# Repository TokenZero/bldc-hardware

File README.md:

VESC – Open Source ESC
=============

Custom board-mount version of the VESC 4.12

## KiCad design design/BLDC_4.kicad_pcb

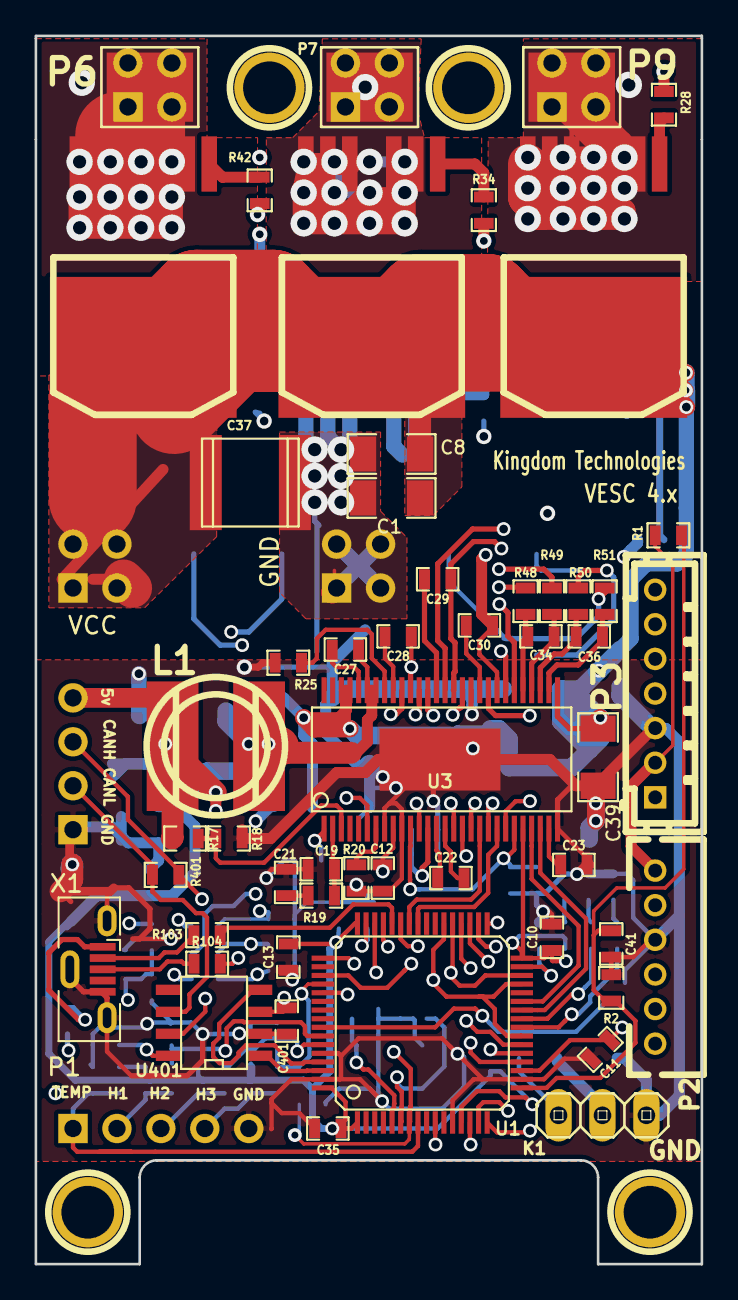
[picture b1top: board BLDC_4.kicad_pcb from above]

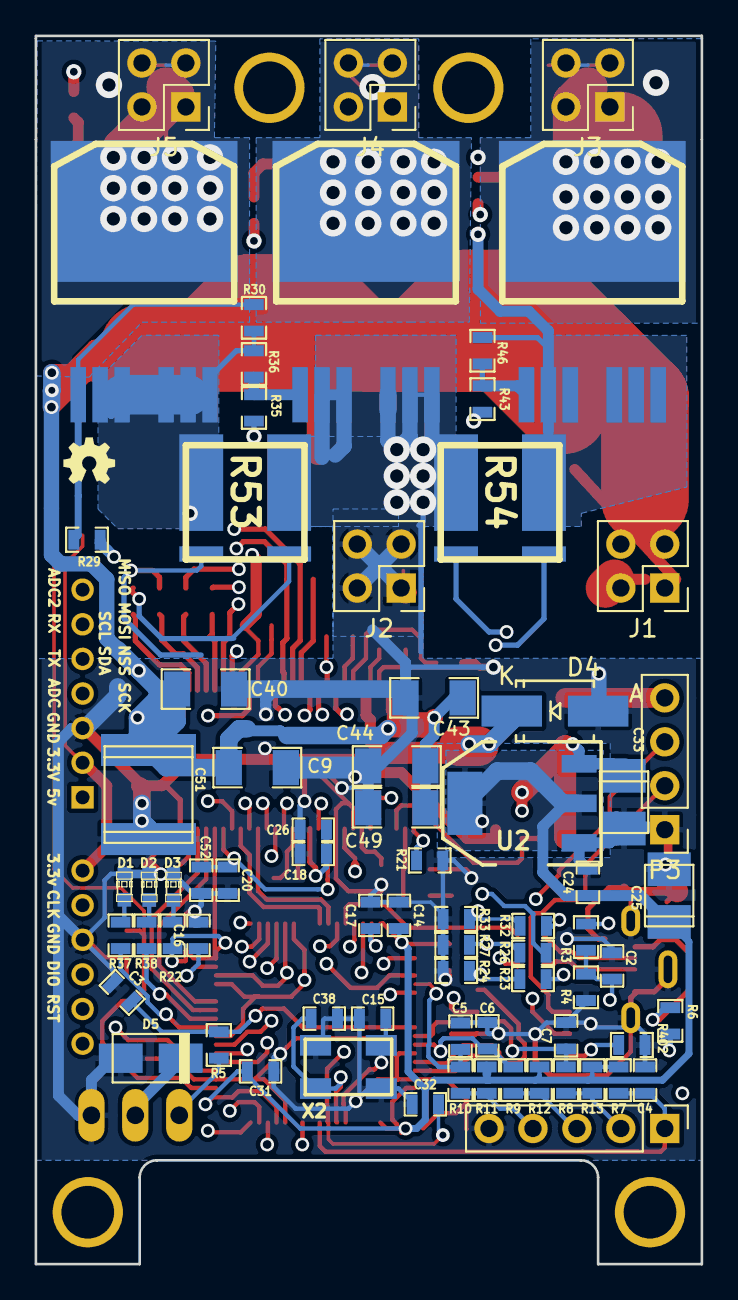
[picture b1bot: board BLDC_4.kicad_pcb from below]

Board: 4 copper layers, 38.5 x 71.0 mm, 129 parts (73 on the bottom side), 96 nets.

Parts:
1PIN, 1PIN#2, 1PIN#3, 1PIN#4: P***; 1pin
C1, C8, C9, C39, C40, C43, C44, C49: 10u,50V; SMD-1206
C2, C3, C27, C32: 100n; SMD-0603_c
C4, C5, C6, C7: 4n7; SMD-0603_c
C10, C11, C12, C13, C14, C16, C17, C18, C20, C23, C24, C26, C31, C35, C41, C52, C401: 2.2u; SMD-0603_c
C15, C38: 15p; SMD-0603_c
C19: 120p; SMD-0603_c
C21: 6.8n; SMD-0603_c
C22: 22n; SMD-0603_c
C25, C33: 100u; c_tant_B
C28, C29, C30: 220n; SMD-0603_c
C34, C36: 2.2n; SMD-0603_c
C37: 15u,100V; c_2220
C51: 15u, 100v; c_2220
D1: GREEN; LED-0603
D2: RED; LED-0603
D3: LED; LED-0603
D4: DIODESCH; SMA_Handsoldering
D5: TVS 5V; do214ac
J1: VCC_IN; PinHeader_2x02_P2.54mm_Vertical
J2: GND_IN; PinHeader_2x02_P2.54mm_Vertical
J3, J4, J5: PinHeader_2x02_P2.54mm_Vertical
K1: SERVO; pinhead-1X03
L1: 22u; inductor_smd_8x5mm
P1: PinHeader_1x05_P2.54mm_Vertical
P2: SWD; MICRO_JST_6
P3: PinHeader_1x04_P2.54mm_Vertical
P3#2: PWR_COMM; b7b-ph-kl
P6: MOTOR1; 1PAD_4x5mm
P7: MOTOR2; 1PAD_4x5mm
P9: MOTOR3; 1PAD_4x5mm
Q1, Q2, Q3, Q4, Q5, Q6: IRFS7530; D2PAK-7-GDS
R1: NTC 10k; SMD-0603_r
R2, R7, R8, R9, R10, R20, R402: 10k; SMD-0603_r
R3, R23, R26, R30, R32, R36, R46: 39k; SMD-0603_r
R4, R5, R11, R12, R13, R22, R24, R27, R33: 2k2; SMD-0603_r
R6: 0R; SMD-0603_r
R17: 18k; SMD-0603_r
R18: 3k3; SMD-0603_r
R19: 15k; SMD-0603_r
R21: 220k; SMD-0603_r
R25: 1M; SMD-0603_r
R28, R29, R34, R35, R42, R43: 4R7; SMD-0603_r
R37, R38, R48, R49, R50, R51: 100R; SMD-0603_r
R53, R54: SHUNT; WSLP2726
R103, R104: 22R; SMD-0603_r
R401: NI; SMD-0603_r
U1: STM32F40X_LQFP64; lqfp64_pad_mod
U2: TC2117; SOT-223
U3: DRV8302; TSSOP-56-PP
U401: SN65HVD232; SOIC-8-W
X1: USB_Micro-B_Molex-105133-0001
X2: 8MHz 10ppm; Crystal_5x3mm

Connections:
+5V: C33.1, D5.2, K1.2, L1.2, P3.4, P3#2.1, R6.2, R17.1, U2.3
/CAN bus transceiver/CANH: P3.3, R401.1, U401.7
/CAN bus transceiver/CANL: P3.2, R401.2, U401.6
/CAN bus transceiver/CAN_RX: U1.61, U401.4
/CAN bus transceiver/CAN_TX: U1.62, U401.1
/Filters/HALL1_IN: P1.2, R8.1, R13.1
/Filters/HALL1_OUT: C7.1, R8.2, U1.58
/Filters/HALL2_IN: P1.3, R9.1, R12.1
/Filters/HALL2_OUT: C6.1, R9.2, U1.59
/Filters/HALL3_IN: P1.4, R10.1, R11.1
/Filters/HALL3_OUT: C5.1, R10.2, U1.52
/Filters/TEMP_IN: C4.2, P1.1, R7.1, U1.8
/MCU/ADC_TEMP: C41.1, R1.2, R2.1, U1.17
/MCU/AN_IN: C2.2, R3.2, R4.2, U1.10
/MCU/BR_SO1: U1.27, U3.25
/MCU/BR_SO2: U1.26, U3.26
/MCU/DC_CAL: U1.33, U3.12
/MCU/EN_GATE: U1.51, U3.16
/MCU/FAULT: U1.53, U3.6
/MCU/H1: U1.43, U3.17
/MCU/H2: U1.42, U3.19
/MCU/H3: U1.41, U3.21
/MCU/L1: U1.36, U3.18
/MCU/L2: U1.35, U3.20
/MCU/L3: U1.34, U3.22
/MCU/LED_GREEN: R37.2, U1.24
/MCU/LED_RED: R38.2, U1.25
/MCU/MISO_ADC_EXT2: P3#2.7, U1.22
/MCU/RX_SCL_MOSI: P3#2.6, U1.23, U1.29, U1.38
/MCU/SCK_ADC_EXT: P3#2.4, U1.21
/MCU/SENS1: R23.2, R24.2, U1.16
/MCU/SENS2: R26.2, R27.2, U1.15
/MCU/SENS3: R32.2, R33.2, U1.14
/MCU/SERVO: C3.2, R5.1, U1.57
/MCU/TX_SDA_NSS: P3#2.5, U1.20, U1.30, U1.37
/MCU/USB_DM: R103.1, U1.44
/MCU/USB_DP: R104.1, U1.45
/Mosfet driver/H1_LOW: Q2.S, R30.1, R36.1, R53.2, U3.44
/Mosfet driver/H1_VS: C28.1, J5.1, J5.2, J5.3, J5.4, P9.1, Q1.S, Q2.D, R32.1, U3.46
/Mosfet driver/H2_VS: C29.1, J4.1, J4.2, J4.3, J4.4, P7.1, Q3.S, Q4.D, R26.1, U3.41
/Mosfet driver/H3_LOW: Q6.S, R46.1, R54.1, U3.34
/Mosfet driver/H3_VS: C30.1, J3.1, J3.2, J3.3, J3.4, P6.1, Q5.S, Q6.D, R23.1, U3.36
/Mosfet driver/M_H1: R28.2, U3.47
/Mosfet driver/M_H2: R34.2, U3.42
/Mosfet driver/M_H3: R42.2, U3.37
/Mosfet driver/M_L1: R29.2, U3.45
/Mosfet driver/M_L2: R35.2, U3.40
/Mosfet driver/M_L3: R43.2, U3.35
/Mosfet driver/SH1_A: R48.1, R54.3
/Mosfet driver/SH1_B: R49.1, R54.4
/Mosfet driver/SH2_A: R50.1, R53.4
/Mosfet driver/SH2_B: R51.1, R53.3
GND: C1.1, C2.1, C3.1, C4.1, C5.2, C6.2, C7.2, C8.1, C9.1, C10.1, C11.1, C12.1, C13.1, C14.1, C15.2, C16.2, C17.2, C18.2, C19.1, C20.1, C21.1, C23.1, C24.2, C25.2, C26.2, C31.1, C32.1, C33.2, C35.1, C37.1, C38.2, C39.1, C40.1, C41.2, C43.2, C44.2, C49.2, C51.1, C52.1, C401.2, D1.2, D2.2, D3.2, D4.1, D5.1, J2.1, J2.2, J2.3, J2.4, K1.3, P1.5, P2.3, P3.1, P3#2.3, Q4.S, R2.2, R4.1, R18.2, R20.2, R21.1, R24.1, R25.1, R27.1, R33.1, R53.1, R54.2, R402.2, U1.12, U1.18, U1.60, U1.63, U2.1, U3.8, U3.10, U3.28, U3.39, U3.57, U401.2, X1.5, X1.6, X2.3
NRST: C32.2, P2.5, U1.7
unnamed: C15.1, U1.5, X2.1
unnamed: C16.1, U1.31
unnamed: C17.1, U1.47
unnamed: C18.1, C26.1, U3.13
unnamed: C19.2, R19.2, U3.2
unnamed: C20.2, C52.2, U3.11, U3.23
unnamed: C21.2, R19.1
unnamed: C22.1, U3.14
unnamed: C22.2, U3.15
unnamed: C23.2, U3.27
unnamed: C27.1, D4.2, L1.1, U3.50, U3.51
unnamed: C27.2, U3.52
unnamed: C28.2, U3.48
unnamed: C29.2, U3.43
unnamed: C30.2, U3.38
unnamed: C34.1, R48.2, U3.33
unnamed: C34.2, R49.2, U3.32
unnamed: C36.1, R50.2, U3.31
unnamed: C36.2, R51.2, U3.30
unnamed: C38.1, U1.6, X2.2
unnamed: D1.1, R37.1
unnamed: D2.1, R38.1
unnamed: D3.1, R22.1
unnamed: K1.1, R5.2
unnamed: Q1.G, R28.1
unnamed: Q2.G, R29.1, R30.2
unnamed: Q3.G, R34.1
unnamed: Q4.G, R35.1, R36.2
unnamed: Q5.G, R42.1
unnamed: Q6.G, R43.1, R46.2
unnamed: R6.1, X1.1
unnamed: R17.2, R18.1, U3.3
unnamed: R20.1, U3.7
unnamed: R21.2, U3.1
unnamed: R25.2, U3.49
unnamed: R103.2, X1.2
unnamed: R104.2, X1.3
unnamed: R402.1, U401.8
SWCLK: P2.2, U1.49
SWDIO: P2.4, U1.46
VCC: C10.2, C11.2, C12.2, C13.2, C14.2, C24.1, C25.1, C31.2, C35.2, C401.1, P2.1, P3#2.2, R1.1, R7.2, R11.2, R12.2, R13.2, R22.2, U1.1, U1.13, U1.19, U1.32, U1.48, U1.64, U2.2, U3.9, U3.24, U401.3
V_SUPPLY: C1.2, C8.2, C9.2, C37.2, C39.2, C40.2, C43.1, C44.1, C49.1, C51.2, J1.1, J1.2, J1.3, J1.4, Q1.D, Q3.D, Q5.D, R3.1, U3.29, U3.53, U3.54

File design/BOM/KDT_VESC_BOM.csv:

"Id";"Designator";"Package";"Quantity";"Designation";"Supplier and ref";
1;"X1";"USB_Micro-B_Molex-105133-0001";1;"USB_Micro-B_Molex-105133-0001";;;
2;"P1";"PinHeader_1x05_P2.54mm_Vertical";1;"PinHeader_1x05_P2.54mm_Vertical";;;
3;"P3";"PinHeader_1x04_P2.54mm_Vertical";1;"PinHeader_1x04_P2.54mm_Vertical";;;
4;"J1";"PinHeader_2x02_P2.54mm_Vertical";1;"VCC_IN";;;
5;"J2";"PinHeader_2x02_P2.54mm_Vertical";1;"GND_IN";;;
6;"J5,J3,J4";"PinHeader_2x02_P2.54mm_Vertical";3;"PinHeader_2x02_P2.54mm_Vertical";;;
7;"D4";"SMA_Handsoldering";1;"DIODESCH";;;
8;"P2";"MICRO_JST_6";1;"SWD";;;
9;"R53,R54";"WSLP2726";2;"SHUNT";;;
10;"D5";"do214ac";1;"TVS 5V";;;
11;"Q5,Q1,Q2,Q3,Q4,Q6";"D2PAK-7-GDS";6;"IRFS7530";;;
12;"X2";"Crystal_5x3mm";1;"8MHz 10ppm";;;
13;"K1";"pinhead-1X03";1;"SERVO";;;
14;"1PIN,1PIN";"1pin";2;"P***";;;
15;"G***";"oshw_silkscreen-back_3mm";1;"oshw_silkscreen-back_3mm";;;
16;"C25,C33";"c_tant_B";2;"100u";;;
17;"C37";"c_2220";1;"15u,100V";;;
18;"C51";"c_2220";1;"15u, 100v";;;
19;"D1";"LED-0603";1;"GREEN";;;
20;"D2";"LED-0603";1;"RED";;;
21;"D3";"LED-0603";1;"LED";;;
22;"L1";"inductor_smd_8x5mm";1;"22u";;;
23;"P6";"1PAD_4x5mm";1;"MOTOR1";;;
24;"P7";"1PAD_4x5mm";1;"MOTOR2";;;
25;"P9";"1PAD_4x5mm";1;"MOTOR3";;;
26;"U1";"lqfp64_pad_mod";1;"STM32F40X_LQFP64";;;
27;"U3";"TSSOP-56-PP";1;"DRV8302";;;
28;"1PIN,1PIN";"1pin";2;"P***";;;
29;"C1,C8,C9,C39,C40,C43,C44,C49";"SMD-1206";8;"10u,50V";;;
30;"R1";"SMD-0603_r";1;"NTC 10k";;;
31;"R2,R7,R8,R9,R10,R20,R402";"SMD-0603_r";7;"10k";;;
32;"R3,R23,R26,R30,R32,R36,R46";"SMD-0603_r";7;"39k";;;
33;"R4,R5,R11,R12,R13,R22,R24,R27,R33";"SMD-0603_r";9;"2k2";;;
34;"R6";"SMD-0603_r";1;"0R";;;
35;"R17";"SMD-0603_r";1;"18k";;;
36;"R18";"SMD-0603_r";1;"3k3";;;
37;"R19";"SMD-0603_r";1;"15k";;;
38;"R21";"SMD-0603_r";1;"220k";;;
39;"R25";"SMD-0603_r";1;"1M";;;
40;"R28,R29,R34,R35,R42,R43";"SMD-0603_r";6;"4R7";;;
41;"R37,R38,R48,R49,R50,R51";"SMD-0603_r";6;"100R";;;
42;"R103,R104";"SMD-0603_r";2;"22R";;;
43;"R401";"SMD-0603_r";1;"NI";;;
44;"U2";"SOT-223";1;"TC2117";;;
45;"U401";"SOIC-8-W";1;"SN65HVD232";;;
46;"P3";"b7b-ph-kl";1;"PWR_COMM";;;
47;"C26,C401,C52,C41,C35,C31,C24,C23,C20,C18,C17,C16,C14,C13,C12,C11,C10";"SMD-0603_c";17;"2.2u";;;
48;"C38,C15";"SMD-0603_c";2;"15p";;;
49;"C36,C34";"SMD-0603_c";2;"2.2n";;;
50;"C32,C27,C3,C2";"SMD-0603_c";4;"100n";;;
51;"C30,C29,C28";"SMD-0603_c";3;"220n";;;
52;"C22";"SMD-0603_c";1;"22n";;;
53;"C21";"SMD-0603_c";1;"6.8n";;;
54;"C19";"SMD-0603_c";1;"120p";;;
55;"C7,C6,C5,C4";"SMD-0603_c";4;"4n7";;;

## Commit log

2021-02-18 Addition of board mount headers and vertical USB connectors
2021-03-05 Cleared out files, updated gerbers, added BOM
